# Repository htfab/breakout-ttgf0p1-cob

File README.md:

# Tiny Tapeout GF 0p1 COB breakout PCB

&emsp;

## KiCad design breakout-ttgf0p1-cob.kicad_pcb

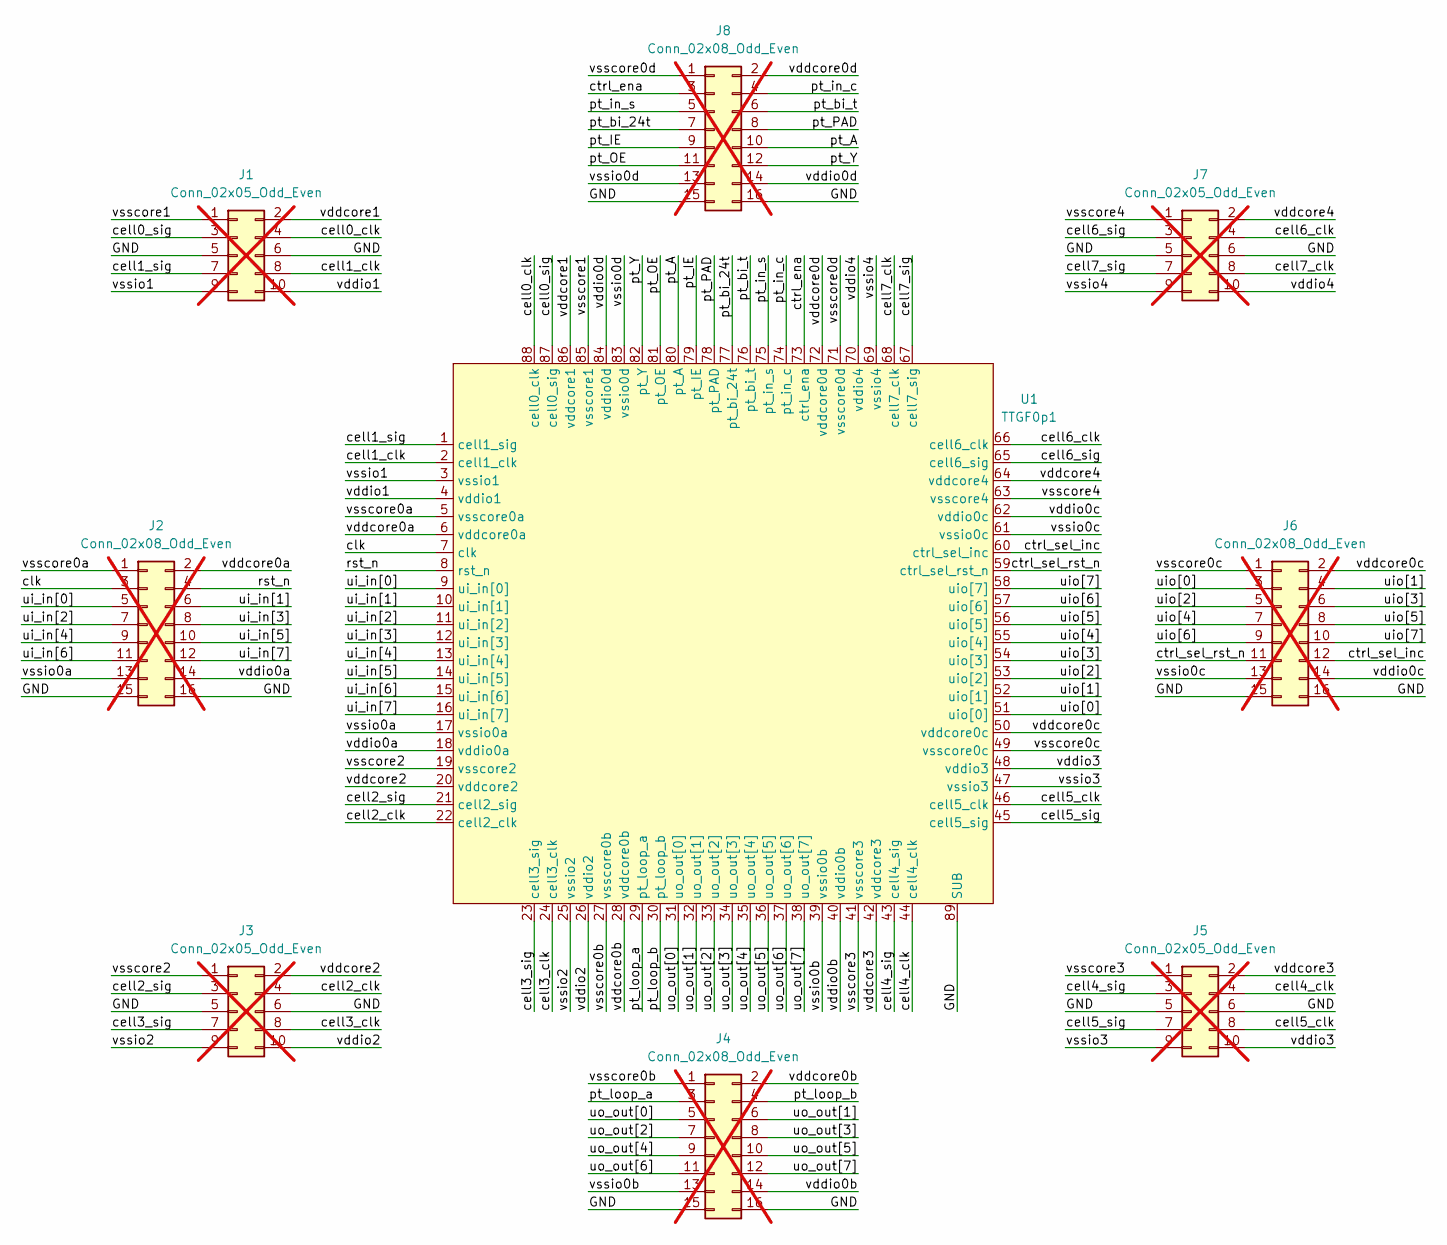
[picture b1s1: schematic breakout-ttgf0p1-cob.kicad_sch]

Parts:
J1, J3, J5, J7: Conn_02x05_Odd_Even; PinHeader_2x05_P2.54mm_Vertical; not fitted
J2, J4, J6, J8: Conn_02x08_Odd_Even; PinHeader_2x08_P2.54mm_Vertical; not fitted
U1: TTGF0p1; ttgf0p1

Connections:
/GND: J1.5, J1.6, J2.15, J2.16, J3.5, J3.6, J4.15, J4.16, J5.5, J5.6, J6.15, J6.16, J7.5, J7.6, J8.15, J8.16, U1.89 (SUB)
/cell0_clk: J1.4, U1.88 (cell0_clk)
/cell0_sig: J1.3, U1.87 (cell0_sig)
/cell1_clk: J1.8, U1.2 (cell1_clk)
/cell1_sig: J1.7, U1.1 (cell1_sig)
/cell2_clk: J3.4, U1.22 (cell2_clk)
/cell2_sig: J3.3, U1.21 (cell2_sig)
/cell3_clk: J3.8, U1.24 (cell3_clk)
/cell3_sig: J3.7, U1.23 (cell3_sig)
/cell4_clk: J5.4, U1.44 (cell4_clk)
/cell4_sig: J5.3, U1.43 (cell4_sig)
/cell5_clk: J5.8, U1.46 (cell5_clk)
/cell5_sig: J5.7, U1.45 (cell5_sig)
/cell6_clk: J7.4, U1.66 (cell6_clk)
/cell6_sig: J7.3, U1.65 (cell6_sig)
/cell7_clk: J7.8, U1.68 (cell7_clk)
/cell7_sig: J7.7, U1.67 (cell7_sig)
/clk: J2.3, U1.7 (clk)
/ctrl_ena: J8.3, U1.73 (ctrl_ena)
/ctrl_sel_inc: J6.12, U1.60 (ctrl_sel_inc)
/ctrl_sel_rst_n: J6.11, U1.59 (ctrl_sel_rst_n)
/pt_A: J8.10, U1.80 (pt_A)
/pt_IE: J8.9, U1.79 (pt_IE)
/pt_OE: J8.11, U1.81 (pt_OE)
/pt_PAD: J8.8, U1.78 (pt_PAD)
/pt_Y: J8.12, U1.82 (pt_Y)
/pt_bi_24t: J8.7, U1.77 (pt_bi_24t)
/pt_bi_t: J8.6, U1.76 (pt_bi_t)
/pt_in_c: J8.4, U1.74 (pt_in_c)
/pt_in_s: J8.5, U1.75 (pt_in_s)
/pt_loop_a: J4.3, U1.29 (pt_loop_a)
/pt_loop_b: J4.4, U1.30 (pt_loop_b)
/rst_n: J2.4, U1.8 (rst_n)
/ui_in[0]: J2.5, U1.9 (ui_in[0])
/ui_in[1]: J2.6, U1.10 (ui_in[1])
/ui_in[2]: J2.7, U1.11 (ui_in[2])
/ui_in[3]: J2.8, U1.12 (ui_in[3])
/ui_in[4]: J2.9, U1.13 (ui_in[4])
/ui_in[5]: J2.10, U1.14 (ui_in[5])
/ui_in[6]: J2.11, U1.15 (ui_in[6])
/ui_in[7]: J2.12, U1.16 (ui_in[7])
/uio[0]: J6.3, U1.51 (uio[0])
/uio[1]: J6.4, U1.52 (uio[1])
/uio[2]: J6.5, U1.53 (uio[2])
/uio[3]: J6.6, U1.54 (uio[3])
/uio[4]: J6.7, U1.55 (uio[4])
/uio[5]: J6.8, U1.56 (uio[5])
/uio[6]: J6.9, U1.57 (uio[6])
/uio[7]: J6.10, U1.58 (uio[7])
/uo_out[0]: J4.5, U1.31 (uo_out[0])
/uo_out[1]: J4.6, U1.32 (uo_out[1])
/uo_out[2]: J4.7, U1.33 (uo_out[2])
/uo_out[3]: J4.8, U1.34 (uo_out[3])
/uo_out[4]: J4.9, U1.35 (uo_out[4])
/uo_out[5]: J4.10, U1.36 (uo_out[5])
/uo_out[6]: J4.11, U1.37 (uo_out[6])
/uo_out[7]: J4.12, U1.38 (uo_out[7])
/vddcore0a: J2.2, U1.6 (vddcore0a)
/vddcore0b: J4.2, U1.28 (vddcore0b)
/vddcore0c: J6.2, U1.50 (vddcore0c)
/vddcore0d: J8.2, U1.72 (vddcore0d)
/vddcore1: J1.2, U1.86 (vddcore1)
/vddcore2: J3.2, U1.20 (vddcore2)
/vddcore3: J5.2, U1.42 (vddcore3)
/vddcore4: J7.2, U1.64 (vddcore4)
/vddio0a: J2.14, U1.18 (vddio0a)
/vddio0b: J4.14, U1.40 (vddio0b)
/vddio0c: J6.14, U1.62 (vddio0c)
/vddio0d: J8.14, U1.84 (vddio0d)
/vddio1: J1.10, U1.4 (vddio1)
/vddio2: J3.10, U1.26 (vddio2)
/vddio3: J5.10, U1.48 (vddio3)
/vddio4: J7.10, U1.70 (vddio4)
/vsscore0a: J2.1, U1.5 (vsscore0a)
/vsscore0b: J4.1, U1.27 (vsscore0b)
/vsscore0c: J6.1, U1.49 (vsscore0c)
/vsscore0d: J8.1, U1.71 (vsscore0d)
/vsscore1: J1.1, U1.85 (vsscore1)
/vsscore2: J3.1, U1.19 (vsscore2)
/vsscore3: J5.1, U1.41 (vsscore3)
/vsscore4: J7.1, U1.63 (vsscore4)
/vssio0a: J2.13, U1.17 (vssio0a)
/vssio0b: J4.13, U1.39 (vssio0b)
/vssio0c: J6.13, U1.61 (vssio0c)
/vssio0d: J8.13, U1.83 (vssio0d)
/vssio1: J1.9, U1.3 (vssio1)
/vssio2: J3.9, U1.25 (vssio2)
/vssio3: J5.9, U1.47 (vssio3)
/vssio4: J7.9, U1.69 (vssio4)

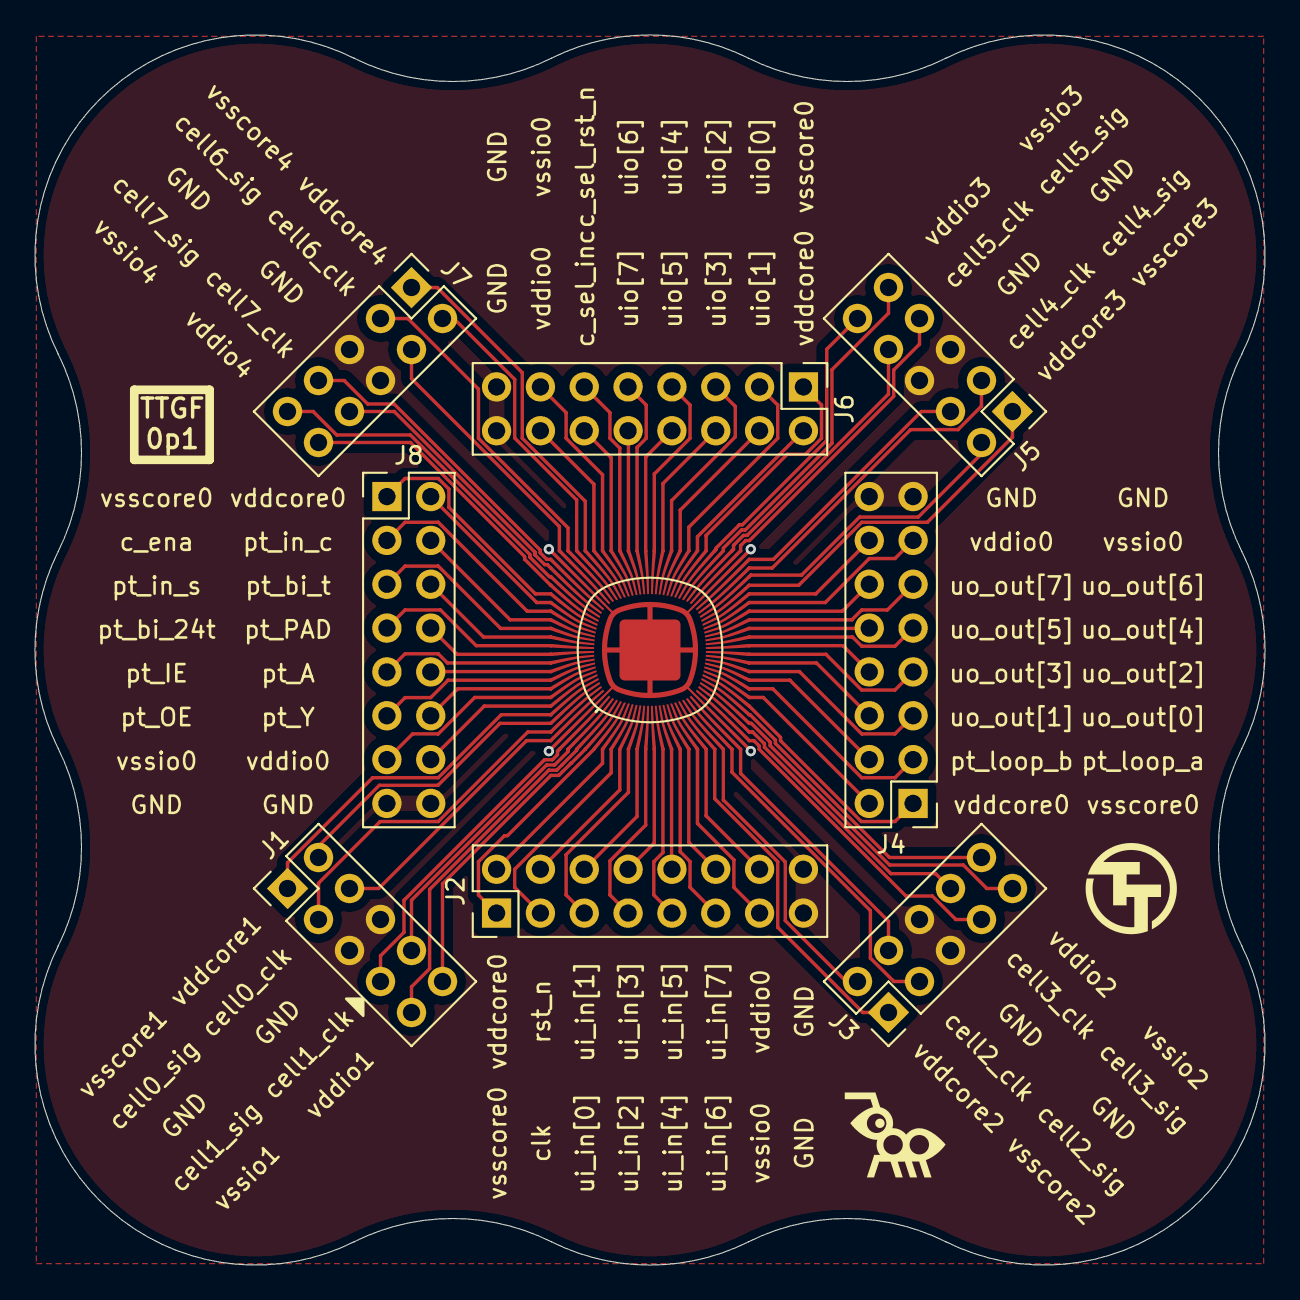
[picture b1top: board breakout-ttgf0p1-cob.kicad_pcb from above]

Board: 2 copper layers, 71.3 x 71.3 mm, 12 parts (1 on the bottom side), 89 nets.

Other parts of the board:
TILL1: Tillitis_logo; tillitis_logo
TTLOGO1, TTLOGO1#2: TT_logo

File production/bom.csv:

Designator,Footprint,Quantity,Value,LCSC Part #
"J1, J3, J5, J7",PinHeader_2x05_P2.54mm_Vertical,4,Conn_02x05_Odd_Even,
"J2, J4, J6, J8",PinHeader_2x08_P2.54mm_Vertical,4,Conn_02x08_Odd_Even,
U1,ttgf0p1,1,TTGF0p1,

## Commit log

2026-03-17 initial version
2026-03-17 add some silkscreen
2026-03-18 rotate cob pcb to match adapter board
2026-03-19 add tillitis logo
2026-03-19 add board images
2026-03-19 add bonding plan
2026-03-19 add readme & license
2026-03-19 add production files
2026-03-19 update ibom config
2026-03-19 update metadata
2026-03-19 exclude DNP components from BOM
